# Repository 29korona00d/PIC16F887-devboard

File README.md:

# PIC16F887-devboard
This is a development board with the Microchip PIC16F887 microcontroller. It contains the chip, a CH340 USB-UART chip, and multiple peripherals.
the PicKit programming pins are connected to pin headers for burning the bootloader in, which is the tiny multi bootloader. Then, it can be programmed through the USB-C. I also included a barrel jack for power supply in case the PC's USB port cant supply enough.
I put a screenshot up for those who would like to see it.

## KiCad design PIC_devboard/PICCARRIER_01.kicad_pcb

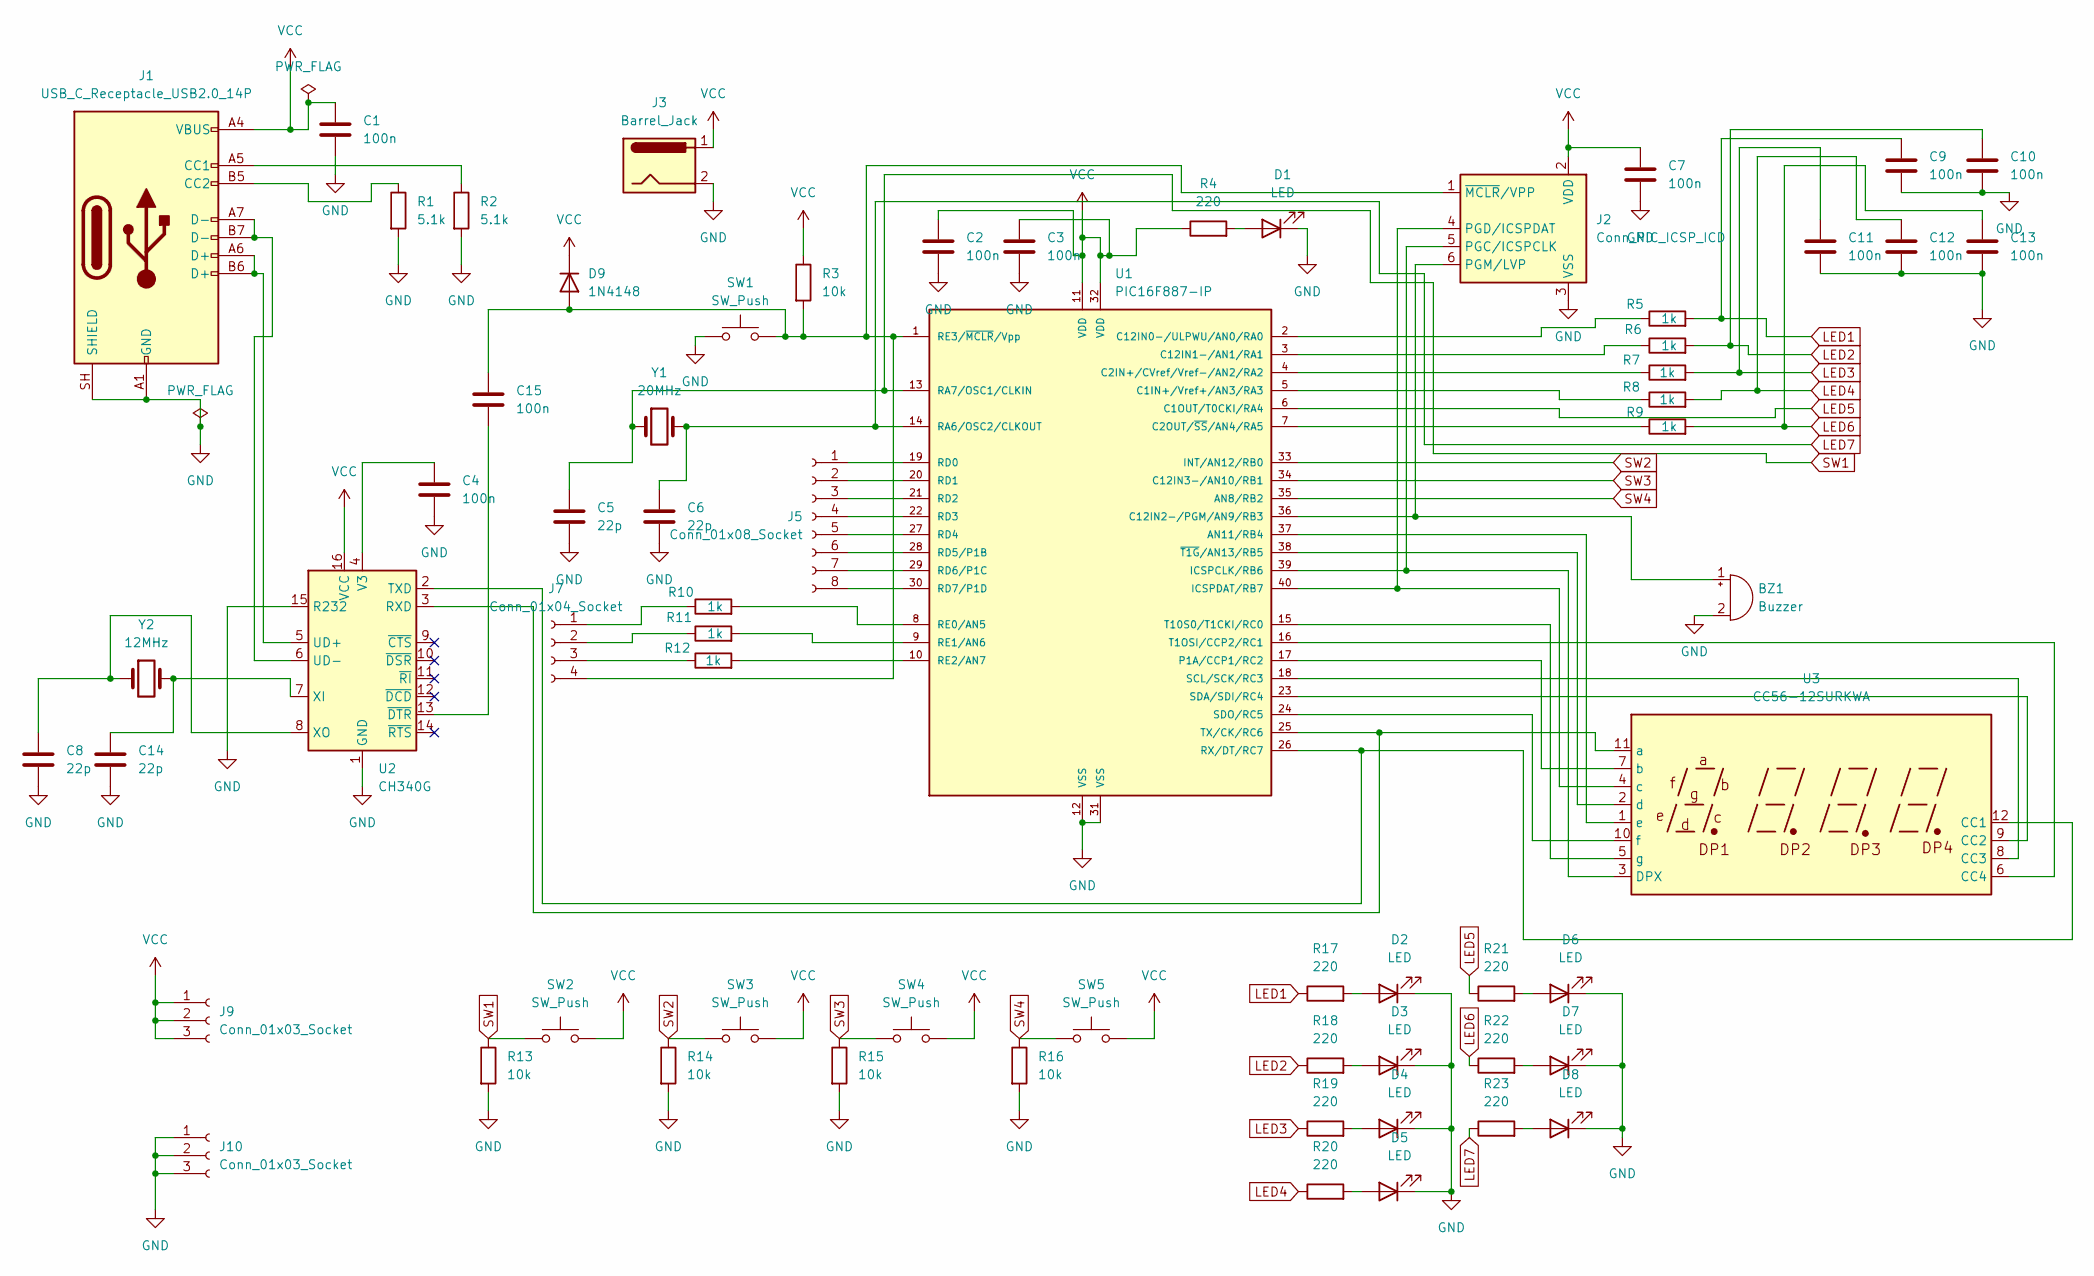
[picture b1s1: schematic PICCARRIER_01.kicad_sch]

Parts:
BZ1: Buzzer; Buzzer_12x9.5RM7.6
C1, C2, C3, C4, C7, C9, C10, C11, C12, C13, C15: 100n; C_0805_2012Metric
C5, C6, C8, C14: 22p; C_0805_2012Metric
D1, D2, D3, D4, D5, D6, D7, D8: LED; LED_0805_2012Metric
D9: 1N4148; D_0805_2012Metric_Pad1.15x1.40mm_HandSolder
J1: USB_C_Receptacle_USB2.0_14P; USB_C_Receptacle_Palconn_UTC16-G
J2: Conn_PIC_ICSP_ICD; PinHeader_1x06_P2.54mm_Vertical
J3: Barrel_Jack; BarrelJack_Horizontal
J5: Conn_01x08_Socket; PinHeader_1x08_P2.54mm_Vertical
J7: Conn_01x04_Socket; PinHeader_1x04_P2.54mm_Vertical
J9, J10: Conn_01x03_Socket; PinHeader_1x03_P2.54mm_Vertical
R1, R2: 5.1k; R_0805_2012Metric
R3, R13, R14, R15, R16: 10k; R_0805_2012Metric
R4, R17, R18, R19, R20, R21, R22, R23: 220; R_0805_2012Metric
R5, R6, R7, R8, R9, R10, R11, R12: 1k; R_0805_2012Metric
SW1, SW2, SW3, SW4, SW5: SW_Push; SW_PUSH_6mm_H5mm
U1: PIC16F887-IP; DIP-40_W15.24mm_Socket
U2: CH340G; SOIC-16_3.9x9.9mm_P1.27mm
U3: CC56-12SURKWA; CA56-12SURKWA
Y1: 20MHz; Crystal_HC49-4H_Vertical
Y2: 12MHz; Crystal_HC49-4H_Vertical

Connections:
GND: BZ1.2 (-), C1.2, C2.2, C3.2, C4.2, C5.2, C6.2, C7.2, C8.2, C9.2, C10.2, C11.2, C12.2, C13.2, C14.2, D1.1 (K), D2.1 (K), D3.1 (K), D4.1 (K), D5.1 (K), D6.1 (K), D7.1 (K), D8.1 (K), J1.A1 (GND), J1.A12 (GND), J1.B1 (GND), J1.B12 (GND), J1.SH (SHIELD), J2.3 (VSS), J3.2, J10.1, J10.2, J10.3, R1.2, R2.2, R13.2, R14.2, R15.2, R16.2, SW1.1, U1.12 (VSS), U1.31 (VSS), U2.1 (GND), U2.15 (R232)
LED1: C9.1, R5.2, R17.1
LED2: C10.1, R6.2, R18.1
LED3: C11.1, R7.2, R19.1
LED4: C12.1, R8.2, R20.1
LED5: R21.1, U1.6 (C1OUT/T0CKI/RA4)
LED6: C13.1, R9.2, R22.1
LED7: C6.1, R23.1, U1.14 (RA6/OSC2/CLKOUT), Y1.2
unnamed: BZ1.1 (+), J2.6 (PGM/LVP), U1.36 (C12IN2-/PGM/AN9/RB3)
unnamed: D1.2 (A), R4.2
unnamed: D2.2 (A), R17.2
unnamed: D3.2 (A), R18.2
unnamed: D4.2 (A), R19.2
unnamed: D5.2 (A), R20.2
unnamed: D6.2 (A), R21.2
unnamed: D7.2 (A), R22.2
unnamed: D8.2 (A), R23.2
unnamed: C15.1, D9.2 (A), J2.1 (~MCLR/VPP), J7.4, R3.2, SW1.2, U1.1 (RE3/~MCLR/Vpp)
unnamed: J1.A5 (CC1), R2.1
unnamed: J1.B5 (CC2), R1.1
unnamed: J2.5 (PGC/ICSPCLK), U1.39 (ICSPCLK/RB6), U3.3 (DPX)
unnamed: J2.4 (PGD/ICSPDAT), U1.40 (ICSPDAT/RB7), U3.4 (c)
unnamed: J5.1, U1.19 (RD0)
unnamed: J5.2, U1.20 (RD1)
unnamed: J5.3, U1.21 (RD2)
unnamed: J5.4, U1.22 (RD3)
unnamed: J5.5, U1.27 (RD4)
unnamed: J5.6, U1.28 (RD5/P1B)
unnamed: J5.7, U1.29 (RD6/P1C)
unnamed: J5.8, U1.30 (RD7/P1D)
unnamed: J7.1, R10.1
unnamed: J7.2, R11.1
unnamed: J7.3, R12.1
unnamed: U1.37 (AN11/RB4), U3.1 (e)
unnamed: R8.1, U1.5 (C1IN+/Vref+/AN3/RA3)
unnamed: R7.1, U1.4 (C2IN+/CVref/Vref-/AN2/RA2)
unnamed: R9.1, U1.7 (C2OUT/~SS/AN4/RA5)
unnamed: R5.1, U1.2 (C12IN0-/ULPWU/AN0/RA0)
unnamed: R6.1, U1.3 (C12IN1-/AN1/RA1)
unnamed: U1.17 (P1A/CCP1/RC2), U3.7 (b)
unnamed: R10.2, U1.8 (RE0/AN5)
unnamed: R11.2, U1.9 (RE1/AN6)
unnamed: R12.2, U1.10 (RE2/AN7)
unnamed: U1.26 (RX/DT/RC7), U2.2 (TXD), U3.12 (CC1)
unnamed: U1.18 (SCL/SCK/RC3), U3.8 (CC3)
unnamed: U1.23 (SDA/SDI/RC4), U3.9 (CC2)
unnamed: U1.24 (SDO/RC5), U3.10 (f)
unnamed: U1.16 (T1OSI/CCP2/RC1), U3.6 (CC4)
unnamed: U1.15 (T10S0/T1CKI/RC0), U3.5 (g)
unnamed: U1.25 (TX/CK/RC6), U2.3 (RXD), U3.11 (a)
unnamed: U1.38 (~T1G/AN13/RB5), U3.2 (d)
unnamed: J1.A6 (D+), J1.B6 (D+), U2.5 (UD+)
unnamed: J1.A7 (D-), J1.B7 (D-), U2.6 (UD-)
unnamed: C4.1, U2.4 (V3)
unnamed: C14.1, U2.7 (XI), Y2.2
unnamed: C8.1, U2.8 (XO), Y2.1
unnamed: C15.2, U2.13 (~DTR)
SW1: C5.1, R13.1, SW2.1, U1.13 (RA7/OSC1/CLKIN), Y1.1
SW2: R14.1, SW3.1, U1.33 (INT/AN12/RB0)
SW3: R15.1, SW4.1, U1.34 (C12IN3-/AN10/RB1)
SW4: R16.1, SW5.1, U1.35 (AN8/RB2)
VCC: C1.1, C2.1, C3.1, C7.1, D9.1 (K), J1.A4 (VBUS), J1.A9 (VBUS), J1.B4 (VBUS), J1.B9 (VBUS), J2.2 (VDD), J3.1, J9.1, J9.2, J9.3, R3.1, R4.1, SW2.2, SW3.2, SW4.2, SW5.2, U1.11 (VDD), U1.32 (VDD), U2.16 (VCC)

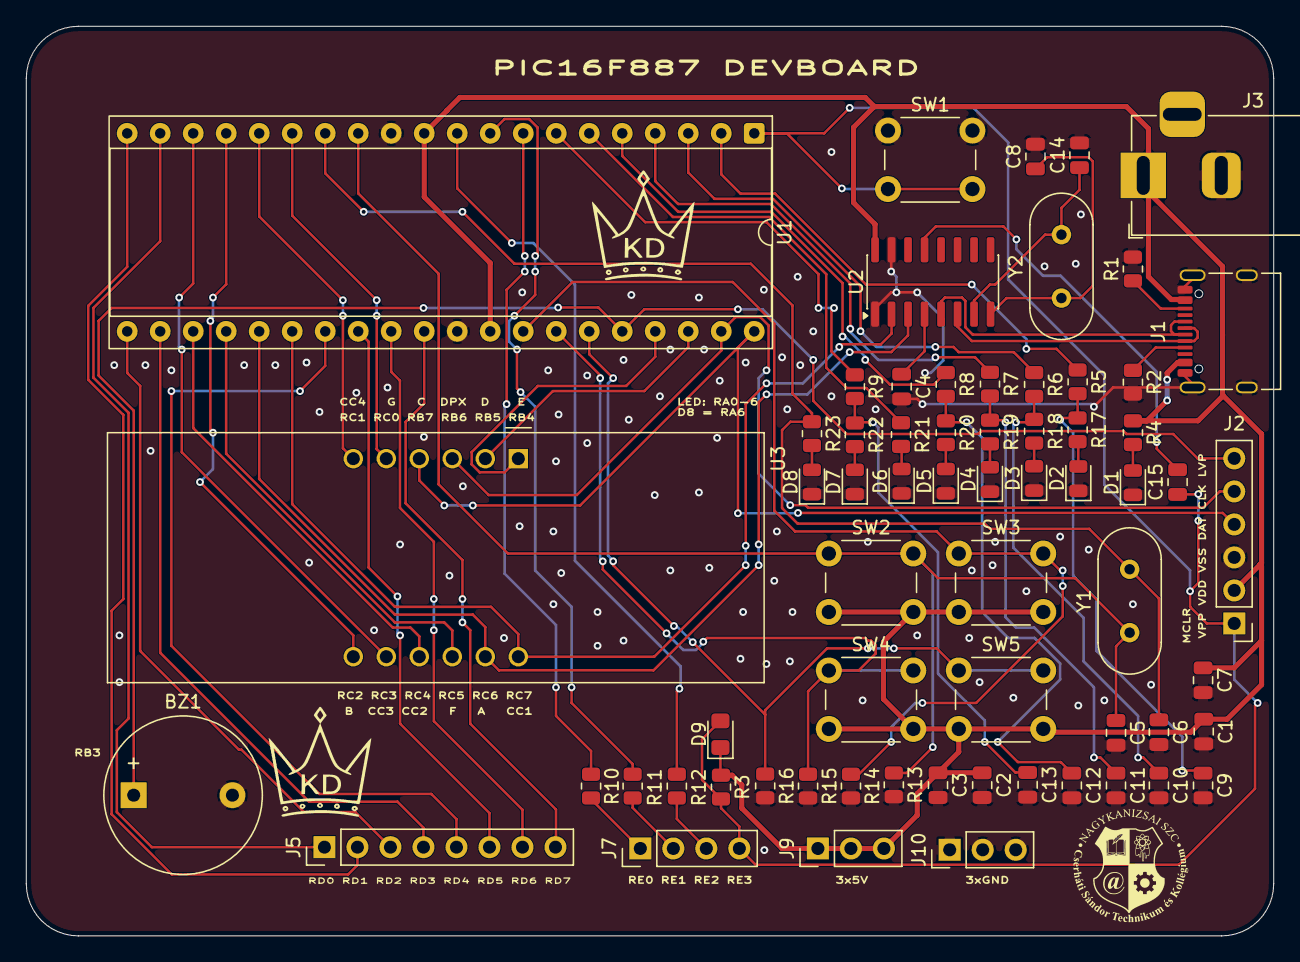
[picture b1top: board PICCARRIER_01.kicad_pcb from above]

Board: 2 copper layers, 96.0 x 70.0 mm, 65 parts (0 on the bottom side), 62 nets.
